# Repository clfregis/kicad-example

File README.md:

# LED Board Example
This is a very basic example of the design of PCB, which contains all files and folder structure that I will use on my KiCAD projects.
## Result

## File structure
```c
/kicad_template
  ↳/bom                         // interactive BOM
  ↳/datasheets                  // data sheets for components used
  ↳/gerber                      // final production files
  ↳/images                      // SVG images and 3D board renders
  ↳/pdf                         // schematics, board layouts, dimension drawings
  ↳kicad_template-cache.lib     // library automatically created by KiCAD
  ↳kicad_template.kicad_pcb     // pcb file
  ↳kicad_template.pro.          // project file
  ↳kicad_template.sch           // schematic file
```
_____________
## Steps in a new design
I always follow this flowchart, works pretty good for me

_____________
## Generating Interactive BOM
 I use this [plugin](https://github.com/openscopeproject/InteractiveHtmlBom), check out the result:

_____________
## Generating Gerber files
 Please refer to this [tutorial](https://support.jlcpcb.com/article/102-kicad-515---generating-gerber-and-drill-files) on JLCPCB website.

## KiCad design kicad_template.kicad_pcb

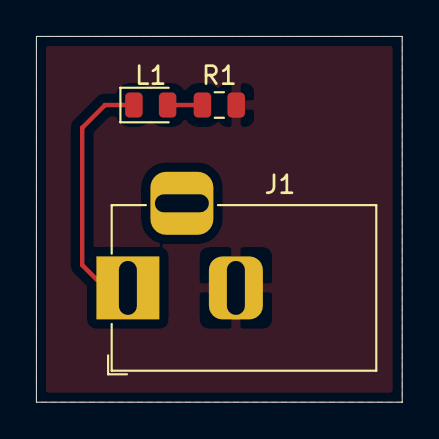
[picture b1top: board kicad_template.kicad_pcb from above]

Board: 2 copper layers, 20.3 x 20.3 mm, 3 parts (0 on the bottom side), 3 nets.

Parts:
J1: Jack-DC; BarrelJack_Horizontal
L1: LED; LED_0805_2012Metric
R1: 1K; R_0805_2012Metric

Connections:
+5V: J1.1, L1.1
GND: J1.2, R1.2
unnamed: L1.2, R1.1

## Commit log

2020-05-30 Adding ibom, datasheets and gerbers
